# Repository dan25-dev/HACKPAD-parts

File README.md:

lom (list of materials)
12x M3x5mx4mm heatset inserts
10x SK6812 MINI-E LEDs (Max 16x)
6x Blank DSA keycaps (White) (2 are spares)
1x 0.91 inch OLED displays
2x EC11 Rotary encoders
6x MX-Style switches (2 are spares)
1x Seeed XIAO RP2040 
15x Through-hole 1N4148 Diodes

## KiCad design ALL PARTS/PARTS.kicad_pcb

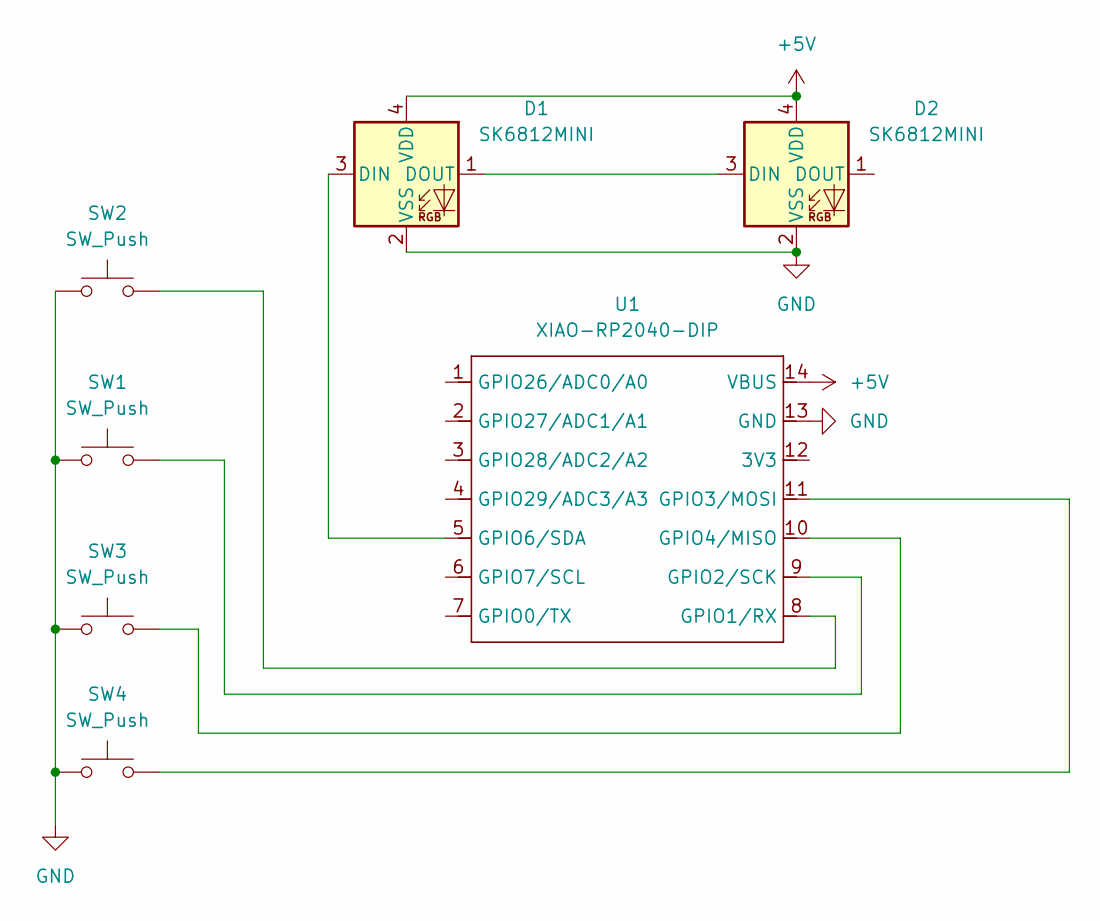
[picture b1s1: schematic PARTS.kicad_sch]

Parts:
D1, D2: SK6812MINI; LED_SK6812MINI_PLCC4_3.5x3.5mm_P1.75mm
SW1, SW2, SW3, SW4: SW_Push; SW_Cherry_MX_1.00u_PCB
U1: XIAO-RP2040-DIP

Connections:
+5V: D1.4 (VDD), D2.4 (VDD), U1.14 (VBUS)
GND: D1.2 (VSS), D2.2 (VSS), SW1.1, SW2.1, SW3.1, SW4.1, U1.13 (GND)
unnamed: D1.3 (DIN), U1.5 (GPIO6/SDA)
unnamed: D1.1 (DOUT), D2.3 (DIN)
unnamed: SW2.2, U1.8 (GPIO1/RX)
unnamed: SW1.2, U1.9 (GPIO2/SCK)
unnamed: SW4.2, U1.11 (GPIO3/MOSI)
unnamed: SW3.2, U1.10 (GPIO4/MISO)

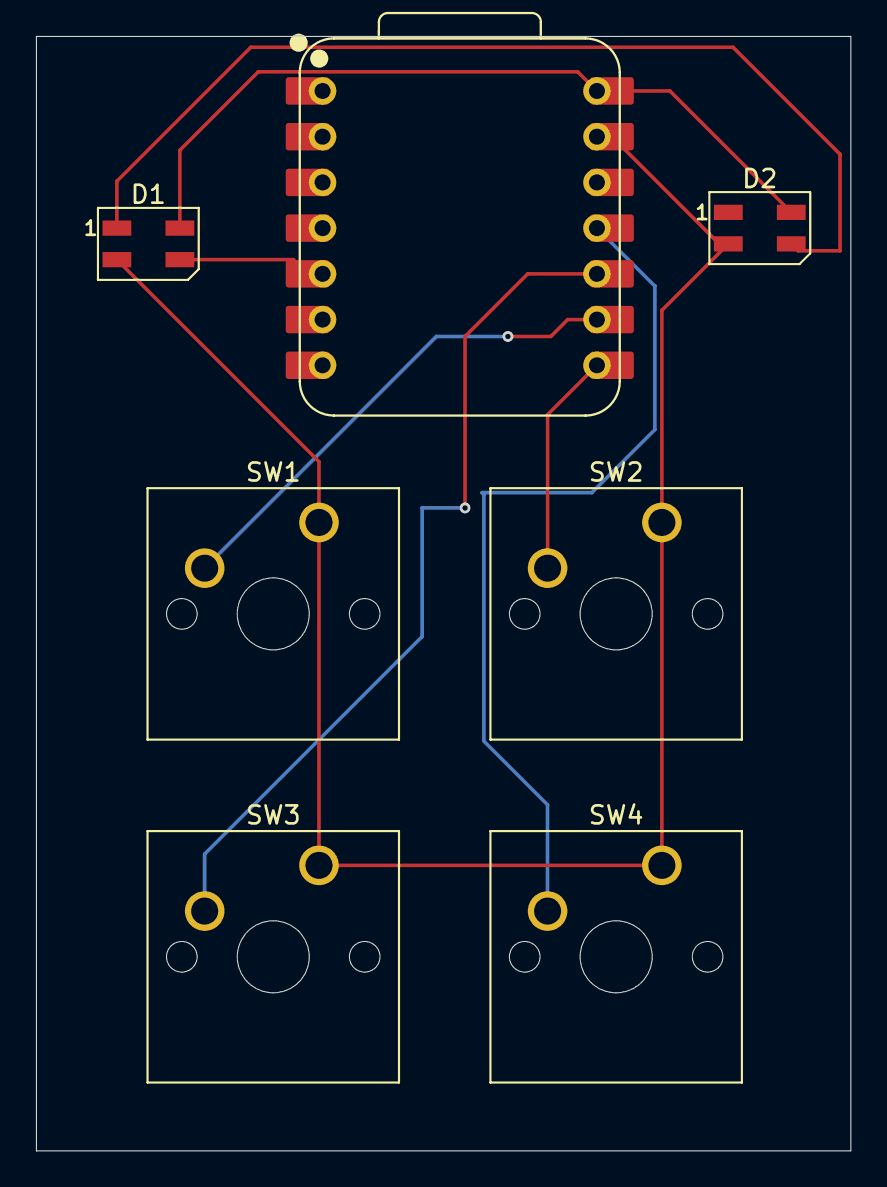
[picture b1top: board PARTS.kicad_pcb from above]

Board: 2 copper layers, 45.2 x 61.9 mm, 7 parts (0 on the bottom side), 8 nets.

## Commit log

2025-12-14 Add initial content to README.md
2025-12-15 README
    Added a list of materials and an image to the README.
2025-12-15 Update README with materials list
2025-12-15 Add additional image to README
    Added a new image to the README for better visualization.
